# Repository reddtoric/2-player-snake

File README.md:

# 2-player-snake

2 player snake game in C++ using Arduino Mega, 32x32 LED matrix, custom shield, and two custom 4-button controllers for Adv. Additive Manufacturing (UIC ENGR 294) with updated case.

</br>

[Original GIF #1](https://media.giphy.com/media/iEMkRfB8JyjEhcMhLR/giphy.gif) | 
[Original GIF #2](https://media.giphy.com/media/J6tbl7obMBHApaVlm7/giphy.gif)

</br></br>

<!-- TOC -->

## Table of Contents

- [2-player-snake](#2-player-snake)
  - [D-pad Controller PCB](#d-pad-controller-pcb)
  - [LED Shield for Arduino Mega](#led-shield-for-arduino-mega)
  - [Case](#case)
  - [Updated Case](#updated-case)

<!-- /TOC -->

(Few more pictures included in _Images/_)

## D-pad Controller PCB

Manually figuring out the routes for all 4 buttons.

Yes, I know the soldering is ugly.

## LED Shield for Arduino Mega

Also manually routed the shield. Here is the mapping of the 16 pin connector socket for LED matrix and the routes to the Arduino Mega pinouts. The correct mapping might be the horizontal mirrored version; I didn't have a connector cable.

I only had access to single sided PCB so red PCB routes are on the top/main side and blue routes are on the back that had to be manually connected with wires.

 </br>

## Case

Planning and designing the controller cases.

(Partially) Initial design. I forgot the divot where the soldering on the PCB takes up space. In the original case, you'll see I melted it. Screw holes and cable hole are not in the CAD because I didn't have enough time to make sure they're were they should be and decided to just drill them.

Putting it all together.

## Updated Case

Added minor changes to the case design. Filet edges, screw holes, tighter tolerances, hole for ethernet cable, and printed with higher quality settings.

Old:

New:

 </br>

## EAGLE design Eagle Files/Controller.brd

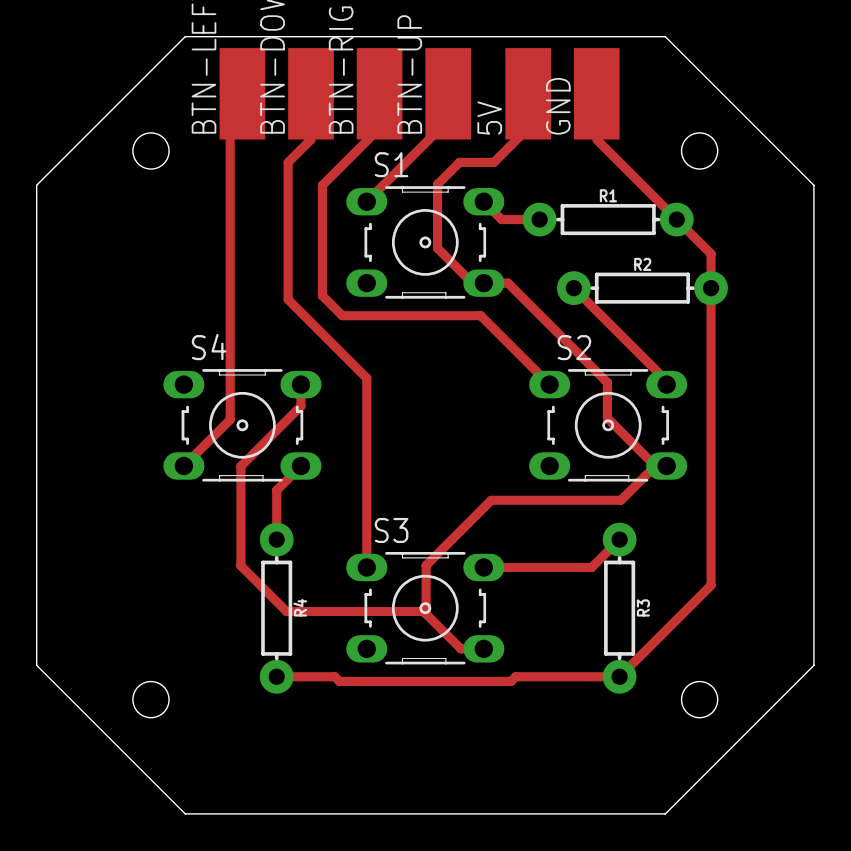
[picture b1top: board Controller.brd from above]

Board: 2 copper layers, 43.2 x 43.2 mm, 14 parts (0 on the bottom side), 10 nets.

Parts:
5V: SMD2,54-5,08
BTN-DOWN: SMD2,54-5,08
BTN-LEFT: SMD2,54-5,08
BTN-RIGHT: SMD2,54-5,08
BTN-UP: SMD2,54-5,08
GND: SMD2,54-5,08
R1, R2, R3, R4: AXIAL-0.3
S1, S2, S3, S4: B3F-10XX

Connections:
unnamed: BTN-DOWN.1, S3.1
unnamed: BTN-RIGHT.1, S2.1
unnamed: BTN-UP.1, S1.1
unnamed: BTN-LEFT.1, S4.3
unnamed: GND.1, R1.P$2, R2.P$2, R3.P$2, R4.P$2
unnamed: R1.P$1, S1.2
unnamed: R2.P$1, S2.2
unnamed: R3.P$1, S3.2
unnamed: R4.P$1, S4.4
unnamed: 5V.1, S1.4, S2.4, S3.4, S4.2

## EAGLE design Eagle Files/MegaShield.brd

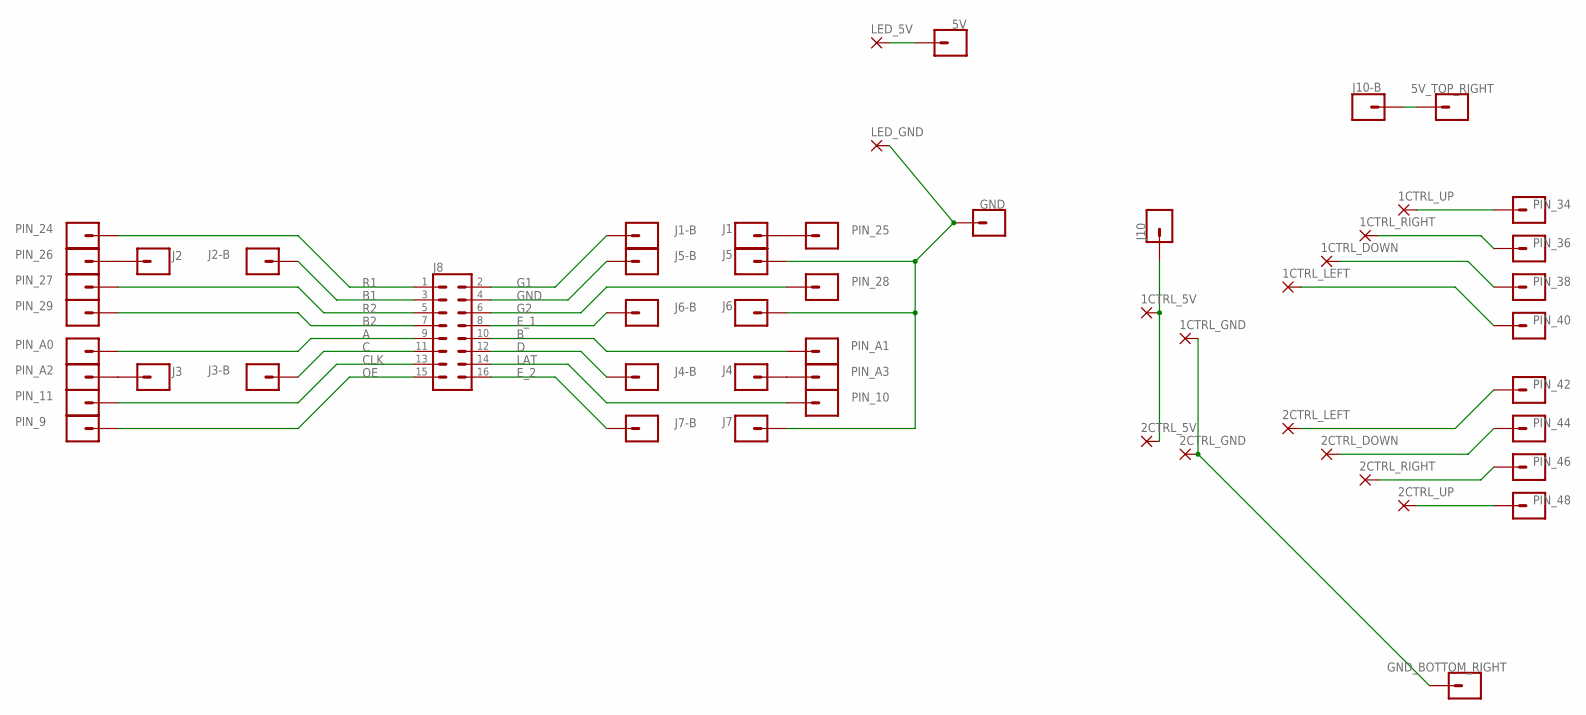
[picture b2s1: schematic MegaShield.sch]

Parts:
1CTRL_5V, 1CTRL_DOWN, 1CTRL_GND, 1CTRL_LEFT, 1CTRL_RIGHT, 1CTRL_UP, 2CTRL_5V, 2CTRL_DOWN, 2CTRL_GND, 2CTRL_LEFT, 2CTRL_RIGHT, 2CTRL_UP: PADSMALL; SMD2,54-5,08
5V, 5V_TOP_RIGHT: CONN_01; 1X01
GND: CONN_01; 1X01
GND_BOTTOM_RIGHT: CONN_01; 1X01
J1, J1-B, J2, J2-B, J3, J3-B, J4, J4-B, J5, J5-B, J6, J6-B, J7, J7-B, J10, J10-B: CONN_01; 1X01
J8: CONN_08X2_SHROUD; 2X8-SHROUDED_LOCK
LED_5V: PAD_EXLARGE; SMD_EXLARGE
LED_GND: PAD_EXLARGE; SMD_EXLARGE
PIN_9, PIN_10, PIN_11, PIN_24, PIN_25, PIN_26, PIN_27, PIN_28, PIN_29, PIN_34, PIN_36, PIN_38, PIN_40, PIN_42, PIN_44, PIN_46, PIN_48: CONN_01; 1X01
PIN_A0, PIN_A1, PIN_A2, PIN_A3: CONN_01; 1X01

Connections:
A: J8.9, PIN_A0.1
B: J8.10, PIN_A1.1
B1: J2-B.1, J8.3
B2: J8.7, PIN_29.1
C: J3-B.1, J8.11
CLK: J8.13, PIN_11.1
D: J4-B.1, J8.12
E_1: J6-B.1, J8.8
E_2: J7-B.1, J8.16
G1: J1-B.1, J8.2
G2: J8.6, PIN_28.1
GND: J5-B.1, J8.4
LAT: J8.14, PIN_10.1
unnamed: J2.1, PIN_26.1
unnamed: J3.1, PIN_A2.1
unnamed: J1.1, PIN_25.1
unnamed: 5V.1, LED_5V.P$1
unnamed: GND.1, J5.1, J6.1, J7.1, LED_GND.P$1
unnamed: J4.1, PIN_A3.1
unnamed: 1CTRL_UP.1, PIN_34.1
unnamed: 1CTRL_RIGHT.1, PIN_36.1
unnamed: 1CTRL_DOWN.1, PIN_38.1
unnamed: 1CTRL_LEFT.1, PIN_40.1
unnamed: 2CTRL_UP.1, PIN_48.1
unnamed: 2CTRL_RIGHT.1, PIN_46.1
unnamed: 2CTRL_DOWN.1, PIN_44.1
unnamed: 5V_TOP_RIGHT.1, J10-B.1
unnamed: 1CTRL_5V.1, 2CTRL_5V.1, J10.1
unnamed: 1CTRL_GND.1, 2CTRL_GND.1, GND_BOTTOM_RIGHT.1
unnamed: 2CTRL_LEFT.1, PIN_42.1
OE: J8.15, PIN_9.1
R1: J8.1, PIN_24.1
R2: J8.5, PIN_27.1

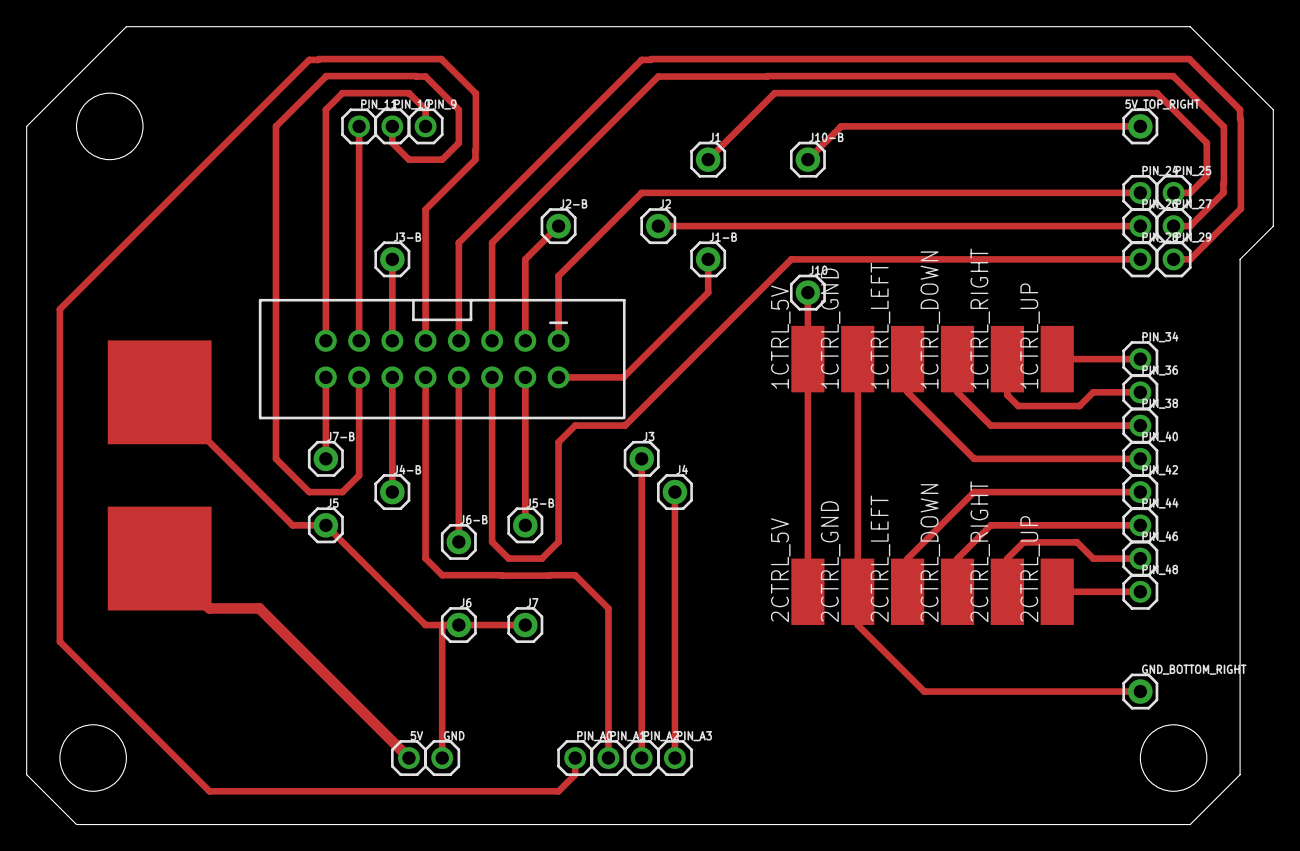
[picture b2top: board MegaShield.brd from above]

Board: 2 copper layers, 95.2 x 61.0 mm, 56 parts (0 on the bottom side), 33 nets.

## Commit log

2018-12-08 original submitted files

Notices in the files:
parts and their libraries:
SparkFun-Connectors: Licensing: Creative Commons ShareAlike 4.0 International - https://creativecommons.org/licenses/by-sa/4.0
